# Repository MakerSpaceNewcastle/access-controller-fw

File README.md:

# RFID_access_controller

[Please see the Project Wiki for more details](https://github.com/davidmpye/RFID_access_controller/wiki)

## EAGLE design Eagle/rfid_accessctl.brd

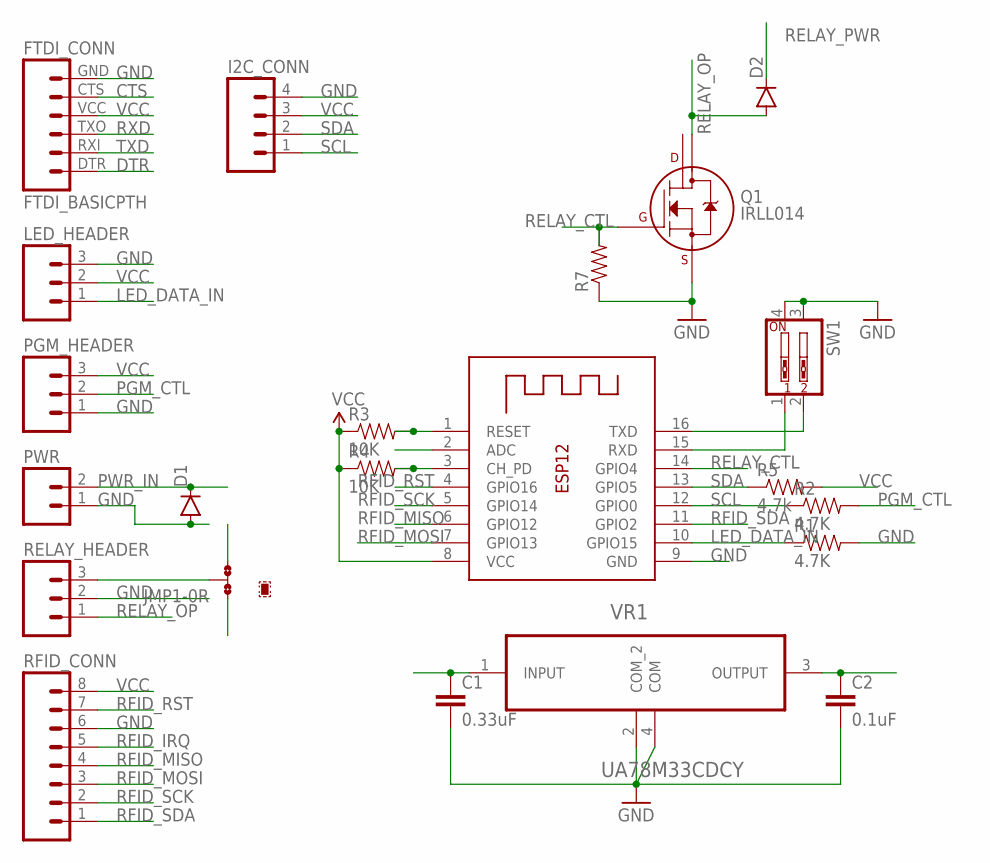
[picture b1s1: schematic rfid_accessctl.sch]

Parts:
C1: 0.33uF; 0805
C2: 0.1uF; 0805
D1, D2: DIODESMA; SMA-DIODE
FTDI_CONN: FTDI_BASICPTH; FTDI_BASIC
I2C_CONN: M04PTH; 1X04
JMP1: 0R-JUMPB; B0R-JMP
LED_HEADER: M03PTH; 1X03
PGM_HEADER: M03PTH; 1X03
PWR: M02PTH; 1X02
Q1: IRLL014; SOT-223
R1, R2: 4.7K; 0603-RES
R3, R4: 10K; 0603-RES
R5: 4.7k; 0603-RES
R7: RESISTOR0603-RES; 0603-RES
RELAY_HEADER: M03PTH; 1X03
RFID_CONN: M08; 1X08_ROUND
SW1: SW_DIP-2-SMT-HALFSIZE; DIPSWITCH-02-50MIL
VR1: UA78M33CDCY; SOT230P700X180-4N
X1: ESP-12

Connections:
CTS: FTDI_CONN.CTS (5)
DTR: FTDI_CONN.DTR (1)
GND: C1.2, C2.2, D1.A, FTDI_CONN.GND (6), I2C_CONN.4, LED_HEADER.3, PGM_HEADER.1, PWR.1, Q1.3 (S), R1.2, R7.1, RELAY_HEADER.2, RFID_CONN.6, SW1.3, SW1.4, VR1.2 (COM_2), VR1.4 (COM), X1.9 (GND)
LED_DATA_IN: LED_HEADER.1, R1.1, X1.10 (GPIO15)
unnamed: R3.2, X1.1 (RESET)
unnamed: R4.2, X1.3 (CH_PD)
PGM_CTL: PGM_HEADER.2, R2.2
PWR_IN: C1.1, D1.C, JMP1.3, PWR.2, VR1.1 (INPUT)
RELAY_CTL: Q1.1 (G), R7.2, X1.14 (GPIO4)
RELAY_OP: D2.A, Q1.2 (D1), RELAY_HEADER.1
RELAY_PWR: D2.C, JMP1.2, RELAY_HEADER.3
RFID_IRQ: RFID_CONN.5
RFID_MISO: RFID_CONN.4, X1.6 (GPIO12)
RFID_MOSI: RFID_CONN.3, X1.7 (GPIO13)
RFID_RST: RFID_CONN.7, X1.4 (GPIO16)
RFID_SCK: RFID_CONN.2, X1.5 (GPIO14)
RFID_SDA: RFID_CONN.1, X1.11 (GPIO2)
RXD: FTDI_CONN.TXO (3), SW1.1, X1.15 (RXD)
SCL: I2C_CONN.1, R2.1, X1.12 (GPIO0)
SDA: I2C_CONN.2, R5.1, X1.13 (GPIO5)
TXD: FTDI_CONN.RXI (2), SW1.2, X1.16 (TXD)
VCC: C2.1, FTDI_CONN.VCC (4), I2C_CONN.3, JMP1.1, LED_HEADER.2, PGM_HEADER.3, R3.1, R4.1, R5.2, RFID_CONN.8, VR1.3 (OUTPUT), X1.8 (VCC)

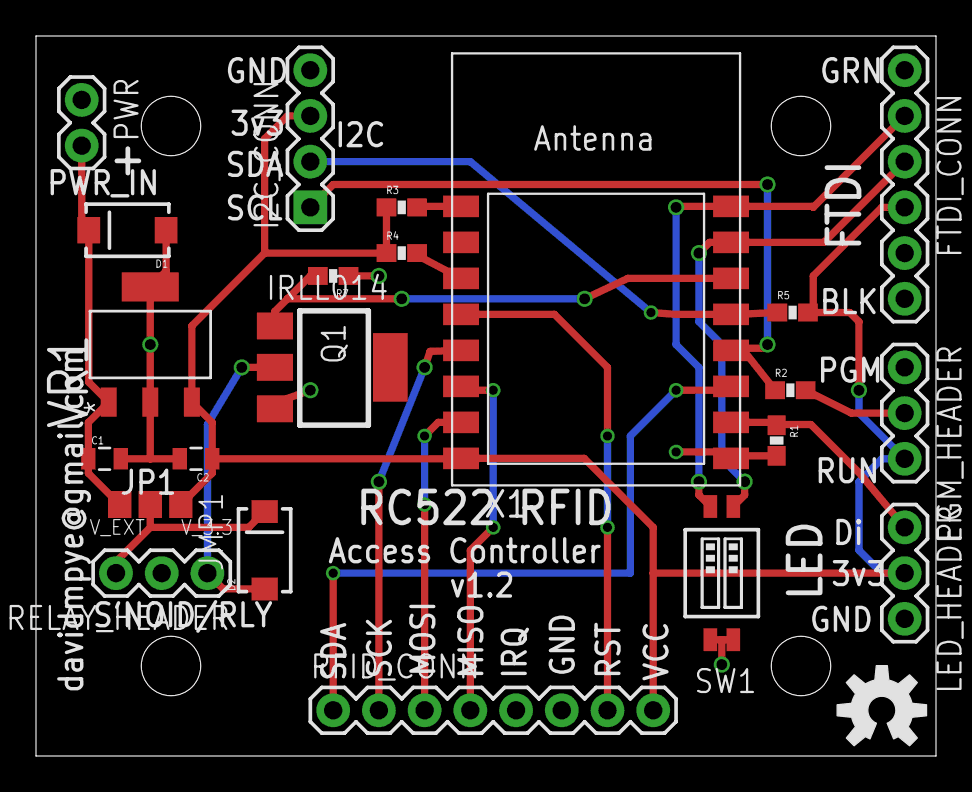
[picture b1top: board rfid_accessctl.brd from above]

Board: 2 copper layers, 50.0 x 40.0 mm, 27 parts (0 on the bottom side), 19 nets.

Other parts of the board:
U$2, U$3, U$4, U$5: STAND-OFF
U$6: OSHW-LOGO-M

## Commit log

2015-12-24 Initial Import
2015-12-24 moved to eagle subdir
2015-12-28 Move screw holes to avoid screws fouling.
2016-01-24 update to v1.1, with fix for I2C/GPIO15
2016-06-21 Start v1.2 board version
2016-06-21 Updates for 0603
2016-06-21 Add DIP switches on serial lines (optional)
2016-06-22 Final updates, as per mfr
2016-07-30 Add initial blank platform.io project shell
2016-07-30 Initial commit of example door opening code
2016-08-01 Add in i2c pin definitions
2016-08-02 Lock/Unlock modes added
2016-08-02 Initial working draft of dual-mode access controller
2016-08-30 DBHandling library for sync/search
2016-08-30 Updates for use with online DB syncing
2016-08-30 More structural realigntment, blue led for resting if on wifi, magenta if offline
2016-09-07 Updates re sync
2016-09-14 Changes for \n terminated records Handle quoted ETag from server
2016-09-14 Sync with MQTT code
2016-09-14 Oops, fix #define for MQTT SUPPORT
2016-09-15 Removed the inSync() test function (not useful and duplicated code). Also ensured ETag/If-None-Match are quoted properly
2016-10-12 First import of laser cut acrylic 3mm case example
2016-10-12 Point to wiki
2016-10-20 Many changes, including OTA update code
2016-10-20 Much redesigning with OTA update support etc.
2016-10-23 Minor change - fix #define, and add small delay for MQTT to connect
2016-10-26 Add cable entry slot
2016-10-26 Fix issue with LED not being reset on latching controllers
2016-10-26 Fix MQTT port error
2016-11-09 Fix URL logging bug (& > ?)
2016-11-09 Add $fn to round holes
2016-11-16 Don't log deactivation/mqtt if it's a non-latching device.
2017-08-10 Added #defines to set LED colours - mainly for stealth mode ;-)
2017-08-24 Add in a reboot 'hack' if the free heap drops <5k. No evidence of a leak that would cause this but a few random hangs have occurred...
2017-08-24 Make the DB update more robust: if any garbled records, or if the Content-Length doesn't match data received, abort the update
2018-02-08 Enhance ETag handling to deal with W/ Etags.
2018-04-17 Add libdeps
2018-04-24 Updated to use the MD5 function from ESP core
2018-12-02 Improve resilience if no wifi available
2018-12-05 Fix copy/paste error
2019-12-04 Reliability/sync updates/reduce timeouts
2019-12-04 Adjust timeout
2019-12-04 Timeout tweaks
2019-12-05 Add gitignore
2019-12-05 Add sample
2020-05-17 Add in WiFi.mode(WIFI_STA) to stop unwanted SSID broadcasts (hopefully)
2022-08-03 add changes for new ESPHttpClient
2022-08-03 Add wificlient
2022-10-05 Update subtle cardreading bug
2022-10-05 Update to LittleFS and squash stack-overload bug
2023-03-07 Make serial debug output conditional
2023-04-12 Add serial mode setting
2023-11-06 Multiple updates: strip out MQTT code, rearrange code to use new backend
2023-11-08 Log timeout increase to 5 seconds, and add hash field to json so the log can include a message
2025-04-26 Add attempted fix to:
    Reset mfrc522 every 255 read cycles
    Set reset pin to UINT8_MAX to indicate unused

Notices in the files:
parts and their libraries:
SparkFun-Connectors: Licensing: Creative Commons ShareAlike 4.0 International - https://creativecommons.org/licenses/by-sa/4.0
